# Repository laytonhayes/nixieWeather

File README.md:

# nixieWeather
Pull down weather data from Wunderground and display using Multiplexed Nixie Tubes

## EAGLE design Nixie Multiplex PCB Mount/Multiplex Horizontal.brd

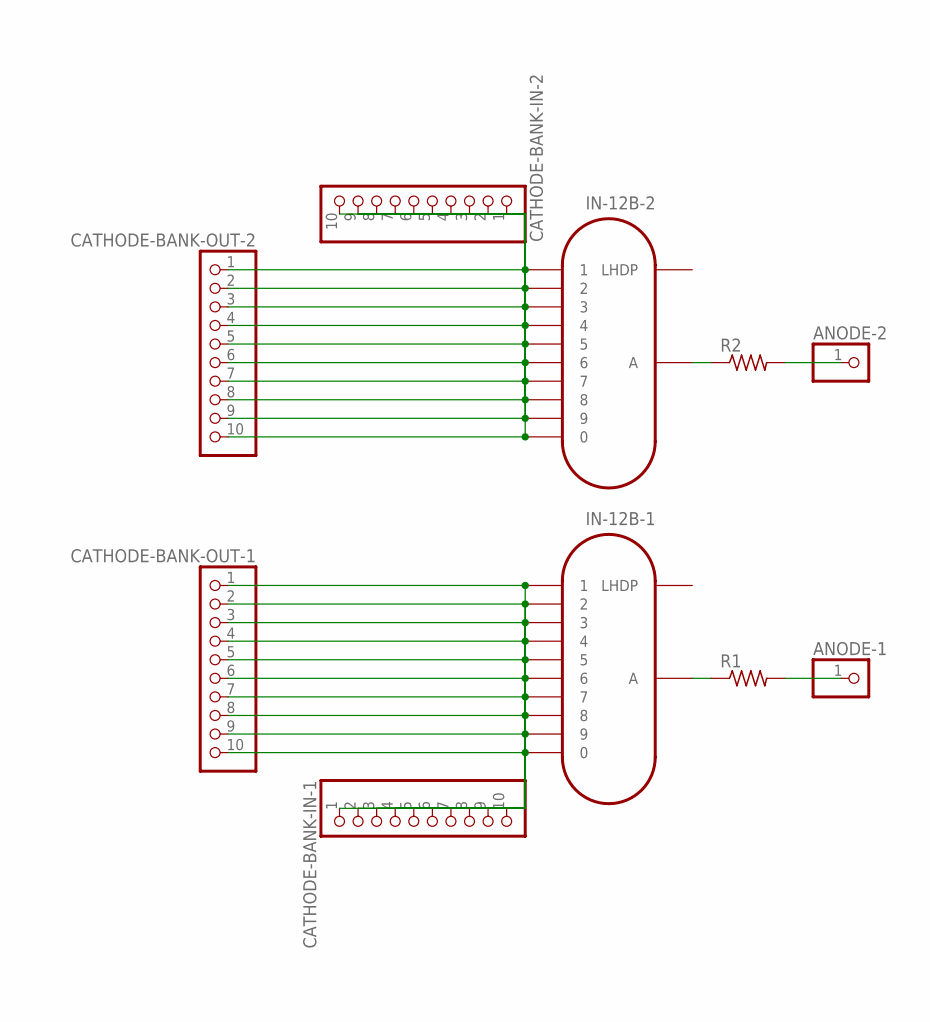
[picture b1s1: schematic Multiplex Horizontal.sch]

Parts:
ANODE-1, ANODE-2: PINHD-1X1; 1X01
CATHODE-BANK-IN-1, CATHODE-BANK-IN-2: PINHD-1X10; 1X10
CATHODE-BANK-OUT-1, CATHODE-BANK-OUT-2: PINHD-1X10; 1X10
IN-12B-1, IN-12B-2: IN-12B; IN-12
R1, R2: R-US_0207/7; 0207/7

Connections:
unnamed: IN-12B-2.A, R2.1
unnamed: CATHODE-BANK-IN-2.1, CATHODE-BANK-OUT-2.1, IN-12B-2.1
unnamed: CATHODE-BANK-IN-2.2, CATHODE-BANK-OUT-2.2, IN-12B-2.2
unnamed: CATHODE-BANK-IN-2.3, CATHODE-BANK-OUT-2.3, IN-12B-2.3
unnamed: IN-12B-1.A, R1.1
unnamed: CATHODE-BANK-IN-2.5, CATHODE-BANK-OUT-2.5, IN-12B-2.5
unnamed: CATHODE-BANK-IN-2.6, CATHODE-BANK-OUT-2.6, IN-12B-2.6
unnamed: CATHODE-BANK-IN-2.7, CATHODE-BANK-OUT-2.7, IN-12B-2.7
unnamed: CATHODE-BANK-IN-2.8, CATHODE-BANK-OUT-2.8, IN-12B-2.8
unnamed: ANODE-2.1, R2.2
unnamed: CATHODE-BANK-IN-2.9, CATHODE-BANK-OUT-2.9, IN-12B-2.9
unnamed: ANODE-1.1, R1.2
unnamed: CATHODE-BANK-IN-1.1, CATHODE-BANK-OUT-1.1, IN-12B-1.1
unnamed: CATHODE-BANK-IN-1.2, CATHODE-BANK-OUT-1.2, IN-12B-1.2
unnamed: CATHODE-BANK-IN-1.3, CATHODE-BANK-OUT-1.3, IN-12B-1.3
unnamed: CATHODE-BANK-IN-1.4, CATHODE-BANK-OUT-1.4, IN-12B-1.4
unnamed: CATHODE-BANK-IN-1.5, CATHODE-BANK-OUT-1.5, IN-12B-1.5
unnamed: CATHODE-BANK-IN-1.6, CATHODE-BANK-OUT-1.6, IN-12B-1.6
unnamed: CATHODE-BANK-IN-1.7, CATHODE-BANK-OUT-1.7, IN-12B-1.7
unnamed: CATHODE-BANK-IN-1.8, CATHODE-BANK-OUT-1.8, IN-12B-1.8
unnamed: CATHODE-BANK-IN-1.9, CATHODE-BANK-OUT-1.9, IN-12B-1.9
unnamed: CATHODE-BANK-IN-2.10, CATHODE-BANK-OUT-2.10, IN-12B-2.0
unnamed: CATHODE-BANK-IN-1.10, CATHODE-BANK-OUT-1.10, IN-12B-1.0
unnamed: CATHODE-BANK-IN-2.4, CATHODE-BANK-OUT-2.4, IN-12B-2.4

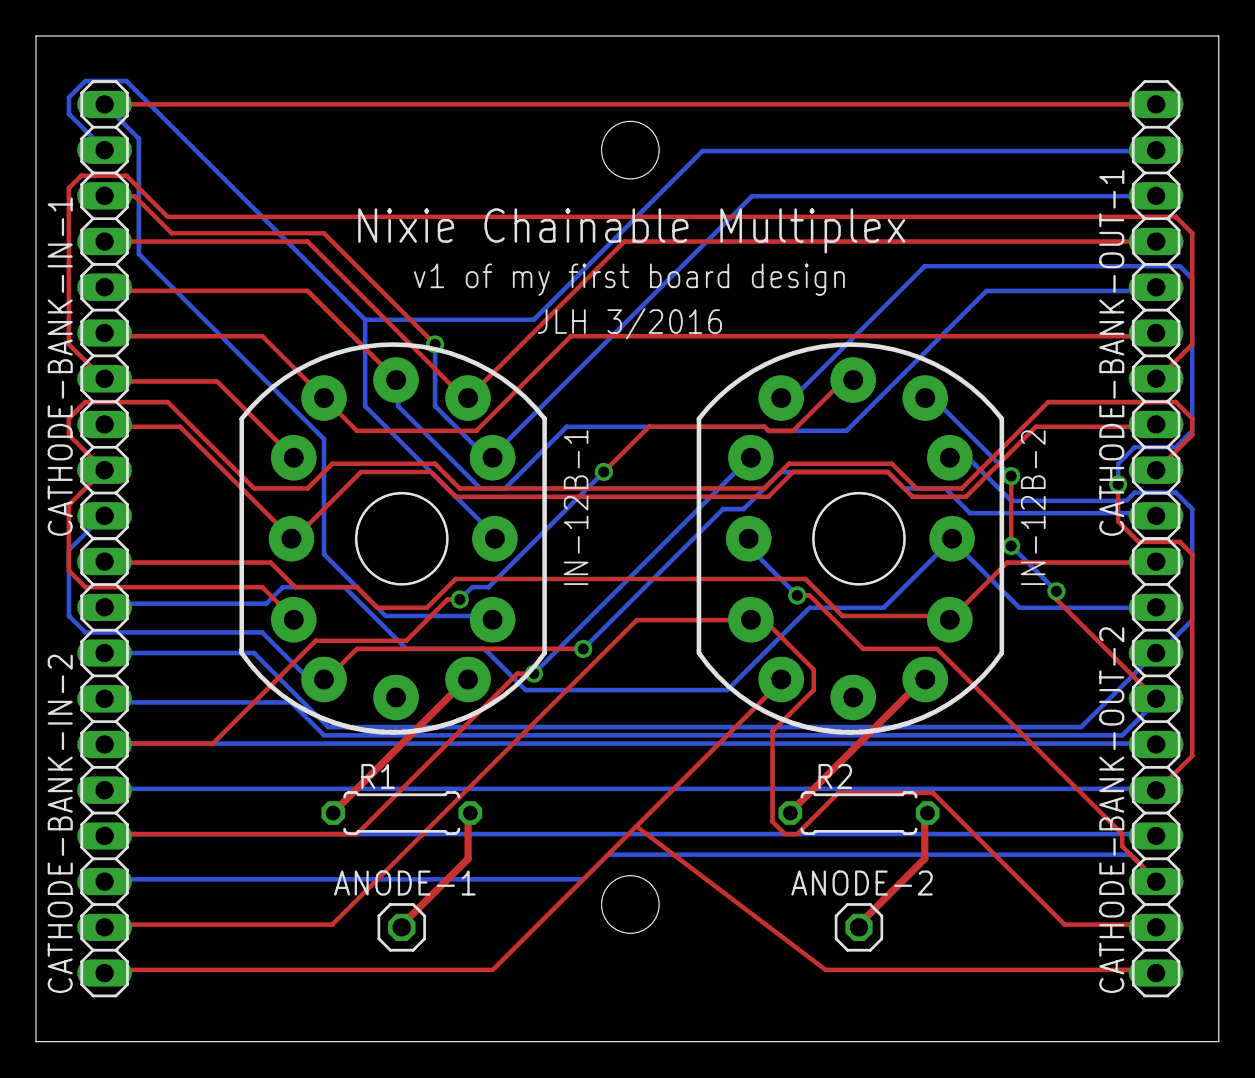
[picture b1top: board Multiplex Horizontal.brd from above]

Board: 2 copper layers, 65.7 x 55.9 mm, 10 parts (0 on the bottom side), 24 nets.

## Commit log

2016-10-27 initial commit with current code status
2016-10-27 organized files and added PCB and case design files
